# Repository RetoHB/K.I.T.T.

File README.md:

# Interactive AI based K.I.T.T. with Voicebox

*Attribution and Acknowledgment:* many thanks to DevMiser for his awesome [DaVinci project](https://github.com/DevMiser/DaVinci)! He laid the foundation for this K.I.T.T project and made it possible in the first place!

This interactive AI based K.I.T.T is a python program that utilizes Picovoice Porcupine (and PyAudio) to detect a wake word; Picovoice Cobra voice activity detection to determine when the user begins and finishes speaking their query; Picovoice Leopard to convert the spoken query to text; OpenAI ChatGPT as the artificial intelligence that responds to the query; Amazon Polly text to speech to convert the response into a natural-sounding human voice; and PyAudio to play the audio. At the same time the voice output is displayed on the voicebox VU meter. The voicebox is attached to the Pi 4 via I2C bus.

Parts required:
- Raspberry Pi 4 – This needs to be a Raspberry Pi 4, so that you can run the 64-bit operating system. Earlier versions of Raspberry Pis are likely to throw memory errors while running this program. Raspberry Pi’s newest OS (Bookworm) released on December 5, 2023, does not work well with this installation. ***For best results, use a Raspberry Pi 4 (not a Raspberry Pi 5) and use the legacy 64-bit OS.*** The 2 GB RAM model is sufficient: https://www.adafruit.com/product/4292
- microSD card, minimum 16GB seems to be a good choice: https://www.adafruit.com/product/2693
- Power Supply – 5V power supply. I recommend the official Raspberry Pi power supply: https://www.adafruit.com/product/4298
- USB Microphone – for talking to K.I.T.T. Any USB mic should work, and this inexpensive one is sufficient: https://www.adafruit.com/product/3367
- USB speaker – for K.I.T.T. to talk back to you. I used this one: https://www.adafruit.com/product/3369
- my [voicebox PCB](voicebox_pcb). I may have some unpoplutaed boards left... contact me
- some nice housing, to be designed...

## Creating required API keys
### Create an OpenAI Account and create a secret key
- Create an account on https://openai.com
- Sign in and click on your personal icon in the upper right-corner and then click on "View API keys". Click on "Create new secret key" and copy the key for later use.

I think you need to make sure to have a positive credit balance in your account. I do not remember if you get a free amount to start with when opening an account.

### Create Picovoice Account and create access key
- Create a free account on https://picovoice.ai
- Sign in and copy your AccessKey for later use

### Create AWS IAM account and obtain AWS access key and secret access key
This is the trickiest step...
- Create a free AWS account on https://aws.amazon.com/free/
- Go to the IAM dashboard under https://console.aws.amazon.com/iamv2
- Select "User groups" from the menu on the left side, then click "Create group" in the upper right corner.
- As group name enter "Polly".
- Under "Attach permission policies - Optional" search for "Polly" and select "AmazonPollyFullAccess".
- Then select "Users" from the menu on the left side and click "Add users" in the upper right corner.
- Type "Polly_User" and click next.
- Under Permission options select "Add user to group" and check the box next to "Polly" under "User groups". Click next.
- Click "Create User" and then "View User".
- In the tab "Security credentials" click "Create access key". Select "Command Line Interface (CLI), tick the box at the bottom and click "Create access key".
- On the next page copy both "Access key" and "Secret access key" for later use.

## Install required software on Raspberry Pi
Edit the bashrc file with `sudo nano ~/.bashrc`  
At the bottom add:
```
# sets a location where the Raspberry Pi OS and Python can look for
# executable/configuration files
export PATH="$HOME/.local/bin:$PATH"
```
Press `Ctrl + x` and answer with `y`  
`sudo reboot` to reboot your Raspberry Pi  
When back up enter the following commands, one by one. Answer with `y` when asked:  
`sudo apt update`  
`sudo apt full-upgrade`  
`pip3 install --upgrade pip`  
`sudo apt-get install portaudio19-dev`  
`pip3 install pyaudio`  
`pip3 install pvrecorder`  
`pip3 install pvporcupine`  
`pip3 install pvcobra`  
`pip3 install pvleopard`  
`pip3 install --upgrade openai`  
`pip3 install boto3`  
`pip3 install awscli`  
`pip3 install sounddevice`  
`pip3 install pydub`  
`sudo reboot`  
The Raspberry Pi reboots again. When back up enter:
`aws configure`  
Enter the keys when asked, for the region name enter the closest to you from this list: https://docs.aws.amazon.com/general/latest/gr/rande.html#regional-endpoints  
`Default output format` can be left emtpy.  

When completed enter `sudo raspi-config` and navigate to `3 Interface Options` -> `Ì4 I2C` and select `Yes`. Hit enter and leave raspi-config.  
`sudo reboot`  
Your Raspberry Pi reboots again.

## Install the K.I.T.T. program
Enter `git clone https://github.com/RetoHB/K.I.T.T..git` (make sure to type the double point before git)  
Enter the directory which has been created by typing `cd K.I.T.T.`  
Modify the keys.py file with `sudo nano keys.py`  
Between the quotations marks enter your personal openai and picovoice keys created earlier. Save and close by hitting `Ctrl + x` and `y`  

## Run the K.I.T.T. program
From within the K.I.T.T. directory type `python kitt.py`to start the program  
Say `hey kitt` to make K.I.T.T. listen to your query. Ask him whatever you want.  
After 15 seconds of silence K.I.T.T. will go to sleep. You can wake him up by saying `hey kitt` again.  

To exit K.I.T.T. hit `Ctrl + c`

## Run the K.I.T.T. program automatically when the Pi starts
For an autostart to be achieved, two steps are required:  
- set the main user to logon automatically when the Pi starts. For this do `sudo raspi-config` navigate to `1 System Options` - `S5 - Boot / Auto Login` -> `B2 - Console Autologin`. Hit `Enter` and `Esc` to leave.
- start the kitt python program whenever a user logs in. Edit `sudo nano ~/.bashrc` and at the very bottom of the file add the line `(cd /home/kitt/K.I.T.T.; python kitt.py &)`. Adjust the path to match your installation.

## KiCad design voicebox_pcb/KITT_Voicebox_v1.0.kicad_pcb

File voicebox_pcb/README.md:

To manufacture this board use the files in the [gerber sub-directory](gerber/).

I may have some unpopulated boards left, contact me in [Discussions](https://github.com/RetoHB/K.I.T.T./discussions/) by mentioning my user name @RetoHB.

The partlist for the components is [here](KITT_Voicebox_v1.0.csv).

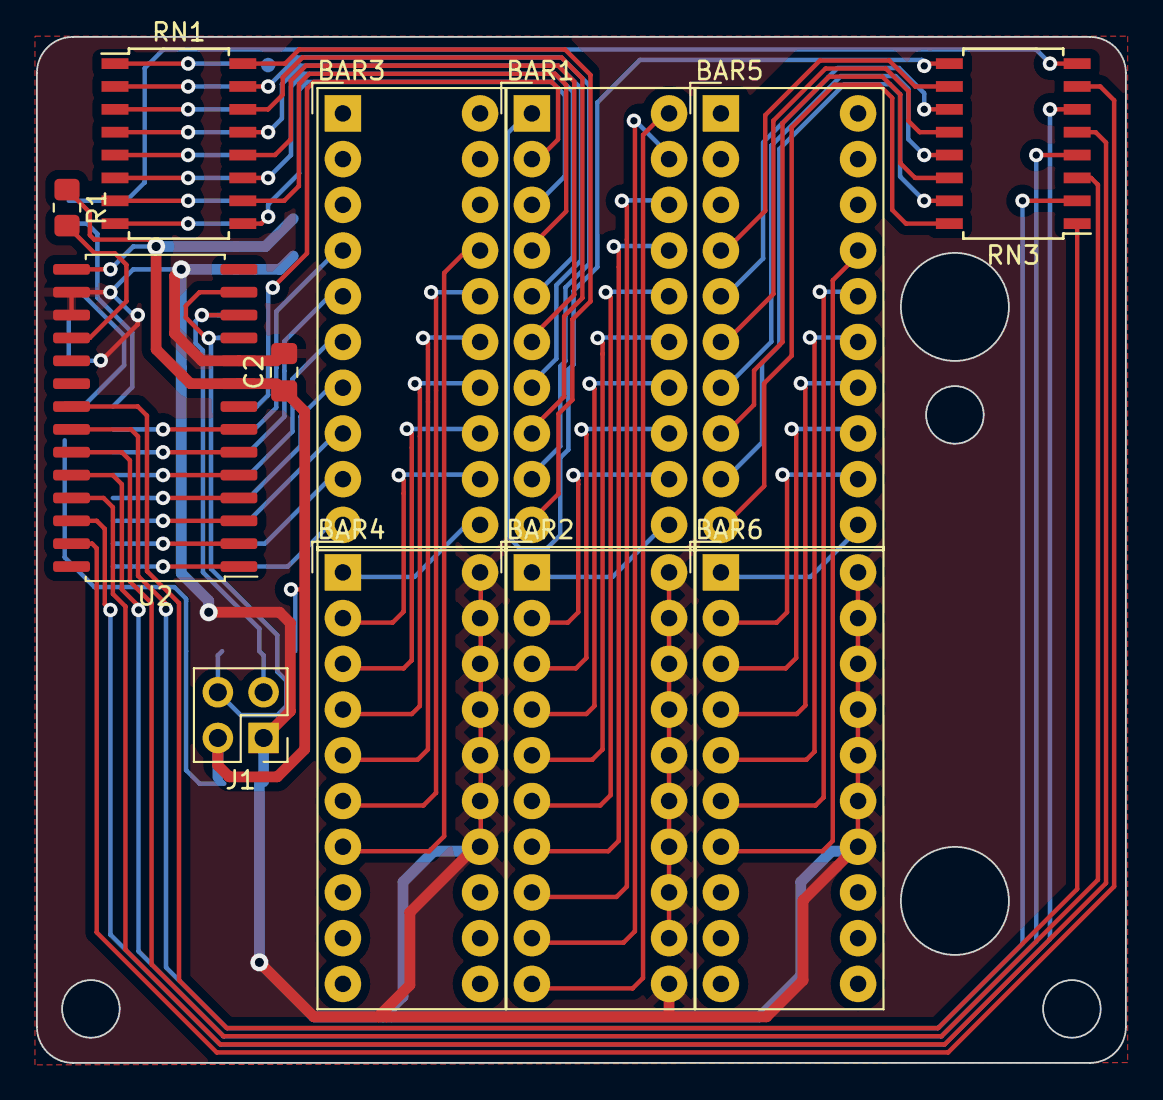
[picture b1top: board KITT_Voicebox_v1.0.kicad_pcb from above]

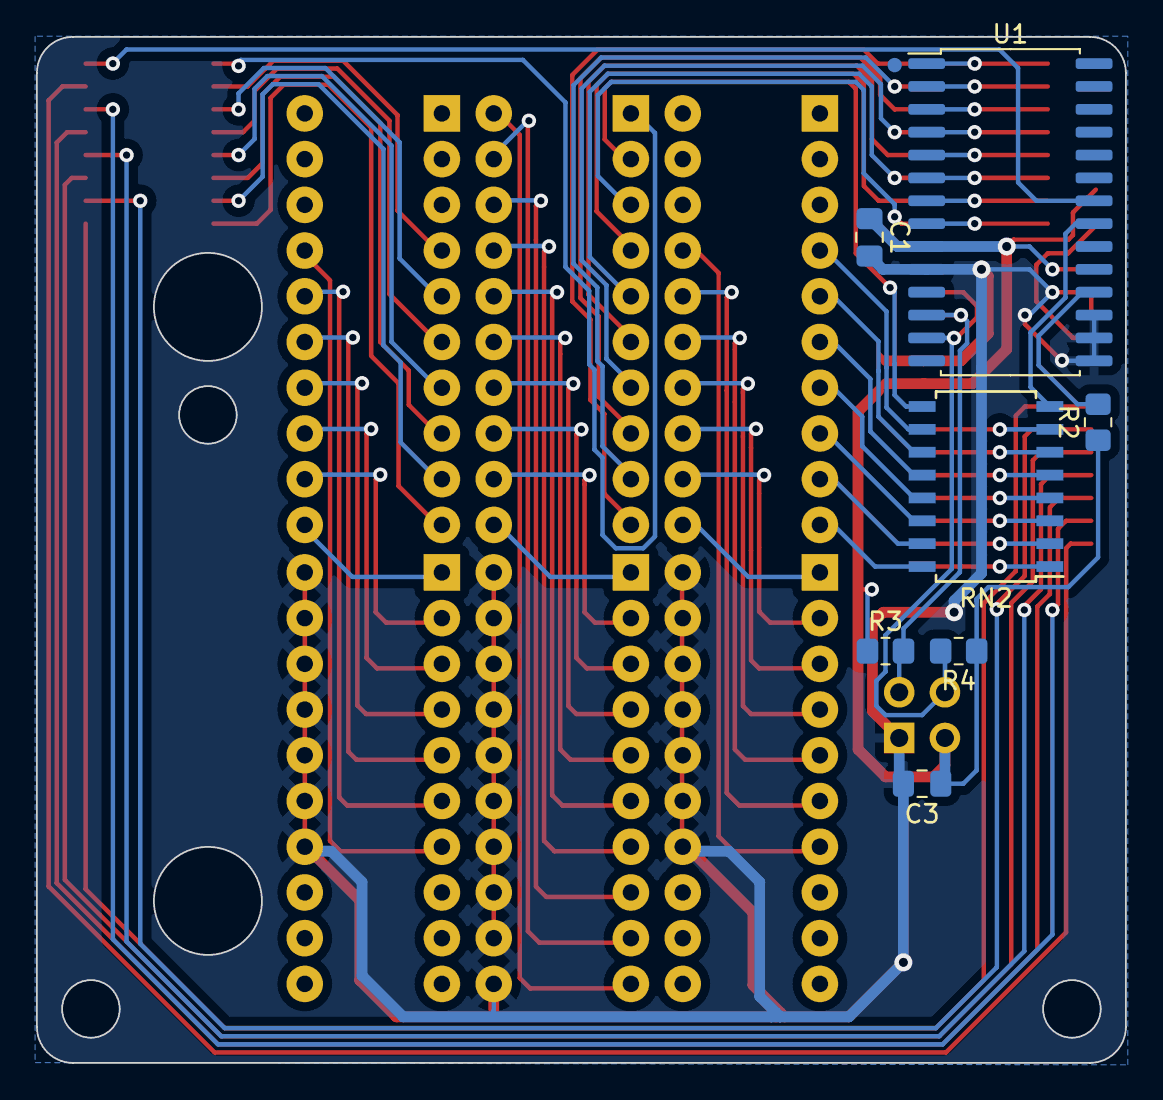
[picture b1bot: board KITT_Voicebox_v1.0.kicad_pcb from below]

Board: 2 copper layers, 60.5 x 57.0 mm, 19 parts (7 on the bottom side), 78 nets.

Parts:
BAR1, BAR2, BAR3, BAR4, BAR5, BAR6: HDSP-4830_2; HDSP-4830
C1, C2: 100nF; C_0805_2012Metric_Pad1.18x1.45mm_HandSolder
C3: 10uF; C_0805_2012Metric_Pad1.18x1.45mm_HandSolder
J1: Conn_02x02_Top_Bottom; PinHeader_2x02_P2.54mm_Vertical
R1, R2, R3, R4: 10k; R_0805_2012Metric_Pad1.20x1.40mm_HandSolder
RN1, RN2, RN3: 8x 68; SOIC-16W_5.3x10.2mm_P1.27mm
U1, U2: MCP23017_SO; SOIC-28W_7.5x17.9mm_P1.27mm

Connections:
+5V: C1.1, C2.1, C3.1, J1.2, R1.1, R2.1, R3.1, R4.1, U1.9 (VDD), U2.9 (VDD), U2.15 (A0)
GND: BAR2.11 (K), BAR2.12 (K), BAR2.13 (K), BAR2.14 (K), BAR2.15 (K), BAR2.16 (K), BAR2.17 (K), BAR2.18 (K), BAR2.19 (K), BAR2.20 (K), BAR4.14 (K), BAR4.15 (K), BAR4.16 (K), BAR4.17 (K), BAR4.18 (K), BAR4.19 (K), BAR4.20 (K), BAR6.14 (K), BAR6.15 (K), BAR6.16 (K), BAR6.17 (K), BAR6.18 (K), BAR6.19 (K), BAR6.20 (K), C1.2, C2.2, C3.2, J1.1, U1.10 (VSS), U1.15 (A0), U1.16 (A1), U1.17 (A2), U2.10 (VSS), U2.16 (A1), U2.17 (A2)
unnamed: BAR1.11 (K), BAR2.1 (A)
unnamed: BAR1.12 (K), BAR2.2 (A)
unnamed: BAR1.13 (K), BAR2.3 (A)
unnamed: BAR1.14 (K), BAR2.4 (A)
unnamed: BAR1.15 (K), BAR2.5 (A)
unnamed: BAR1.16 (K), BAR2.6 (A)
unnamed: BAR1.17 (K), BAR2.7 (A)
unnamed: BAR1.18 (K), BAR2.8 (A)
unnamed: BAR1.19 (K), BAR2.9 (A)
unnamed: BAR1.20 (K), BAR2.10 (A)
unnamed: BAR3.11 (K), BAR4.1 (A)
unnamed: BAR3.12 (K), BAR4.2 (A)
unnamed: BAR3.13 (K), BAR4.3 (A)
unnamed: BAR3.14 (K), BAR4.4 (A)
unnamed: BAR3.15 (K), BAR4.5 (A)
unnamed: BAR3.16 (K), BAR4.6 (A)
unnamed: BAR3.17 (K), BAR4.7 (A)
unnamed: BAR5.11 (K), BAR6.1 (A)
unnamed: BAR5.12 (K), BAR6.2 (A)
unnamed: BAR5.13 (K), BAR6.3 (A)
unnamed: BAR5.14 (K), BAR6.4 (A)
unnamed: BAR5.15 (K), BAR6.5 (A)
unnamed: BAR5.16 (K), BAR6.6 (A)
unnamed: BAR5.17 (K), BAR6.7 (A)
unnamed: J1.3, R3.2, U1.12 (SCK), U2.12 (SCK)
unnamed: J1.4, R4.2, U1.13 (SDA), U2.13 (SDA)
unnamed: RN1.1 (R1.1), U1.1 (GPB0)
unnamed: BAR1.10 (A), RN1.16 (R1.2)
unnamed: RN1.2 (R2.1), U1.2 (GPB1)
unnamed: BAR1.9 (A), RN1.15 (R2.2)
unnamed: RN1.3 (R3.1), U1.3 (GPB2)
unnamed: BAR1.8 (A), RN1.14 (R3.2)
unnamed: RN1.4 (R4.1), U1.4 (GPB3)
unnamed: BAR1.7 (A), RN1.13 (R4.2)
unnamed: RN1.5 (R5.1), U1.5 (GPB4)
unnamed: BAR1.6 (A), RN1.12 (R5.2)
unnamed: RN1.6 (R6.1), U1.6 (GPB5)
unnamed: BAR1.5 (A), RN1.11 (R6.2)
unnamed: RN1.7 (R7.1), U1.7 (GPB6)
unnamed: BAR1.4 (A), RN1.10 (R7.2)
unnamed: RN1.8 (R8.1), U1.8 (GPB7)
unnamed: BAR1.3 (A), RN1.9 (R8.2)
unnamed: RN2.1 (R1.1), U2.1 (GPB0)
unnamed: BAR3.10 (A), RN2.16 (R1.2)
unnamed: RN2.2 (R2.1), U2.2 (GPB1)
unnamed: BAR3.9 (A), RN2.15 (R2.2)
unnamed: RN2.3 (R3.1), U2.3 (GPB2)
unnamed: BAR3.8 (A), RN2.14 (R3.2)
unnamed: RN2.4 (R4.1), U2.4 (GPB3)
unnamed: BAR3.7 (A), RN2.13 (R4.2)
unnamed: RN2.5 (R5.1), U2.5 (GPB4)
unnamed: BAR3.6 (A), RN2.12 (R5.2)
unnamed: RN2.6 (R6.1), U2.6 (GPB5)
unnamed: BAR3.5 (A), RN2.11 (R6.2)
unnamed: RN2.7 (R7.1), U2.7 (GPB6)
unnamed: BAR3.4 (A), RN2.10 (R7.2)
unnamed: RN3.1 (R1.1), U2.21 (GPA0)
unnamed: BAR5.10 (A), RN3.16 (R1.2)
unnamed: RN3.2 (R2.1), U2.22 (GPA1)
unnamed: BAR5.9 (A), RN3.15 (R2.2)
unnamed: RN3.3 (R3.1), U2.23 (GPA2)
unnamed: BAR5.8 (A), RN3.14 (R3.2)
unnamed: RN3.4 (R4.1), U2.24 (GPA3)
unnamed: BAR5.7 (A), RN3.13 (R4.2)
unnamed: RN3.5 (R5.1), U2.25 (GPA4)
unnamed: BAR5.6 (A), RN3.12 (R5.2)
unnamed: RN3.6 (R6.1), U2.26 (GPA5)
unnamed: BAR5.5 (A), RN3.11 (R6.2)
unnamed: RN3.7 (R7.1), U2.27 (GPA6)
unnamed: BAR5.4 (A), RN3.10 (R7.2)
unnamed: R2.2, U1.18 (~RESET)
unnamed: R1.2, U2.18 (~RESET)
R11: RN2.8 (R8.1), U1.21 (GPA0)
R12: BAR1.2 (A), RN2.9 (R8.2)
R21: RN3.8 (R8.1), U1.22 (GPA1)
R22: BAR1.1 (A), RN3.9 (R8.2)

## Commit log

2024-01-29 inital commit
2024-01-31 line removed
2024-01-31 line deleted
2024-01-31 visual ready display added
2024-03-19 modified: kitt.py modified: vu_meter/amplitude.py deleted: vu_meter/vu_constants.py modified: vu_meter/vu_meter.py
